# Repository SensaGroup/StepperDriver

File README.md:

# SENSA Smart Stepper Driver 

### Main features
- on-board ATMEGA328/P
- A4988 module 
- CAN Bus - MCP25625
- Encoder and switch support

## What is the SENSA Smart Stepper Driver?
The SENSA Smart Stepper Driver is an add-on module for a stepper motor and houses all features needed to gain full control of your stepper motor.
Next to the on-board CAN Bus, the driver can also be controlled through USART or I2C.

### ATMEGA328/P
The ATMEGA328/P controls the whole board which is equipped with the Arduino platform.
It runs our [open-source code](), which can be easily modified for any project.

### A4988 module
We have chosen the easily accessible A4988 stepper driver module. It has all features that are needed and it is easy to control.

### MCP25625
The CAN Bus is a very robust communication protocol, which supports up to 1Mb/s speeds and it only requires 3 wires for it to work (CANH, CANL, GND).
The [MCP25625](http://ww1.microchip.com/downloads/en/DeviceDoc/20005282B.pdf) is a CAN controller with an integrated transceiver, meaning it doesn't take up much space.

### Encoder and switches
We have added a connector for an encoder, whose pins are connected to interrupt pins of the ATMEGA328/P. 
Two switches can be also added to the board via a connector, which can help you add control to your project. 

## Images

## Sponsored by AISLER
### Develop and manufacture your own premium boards at [aisler.net](https://aisler.net/)

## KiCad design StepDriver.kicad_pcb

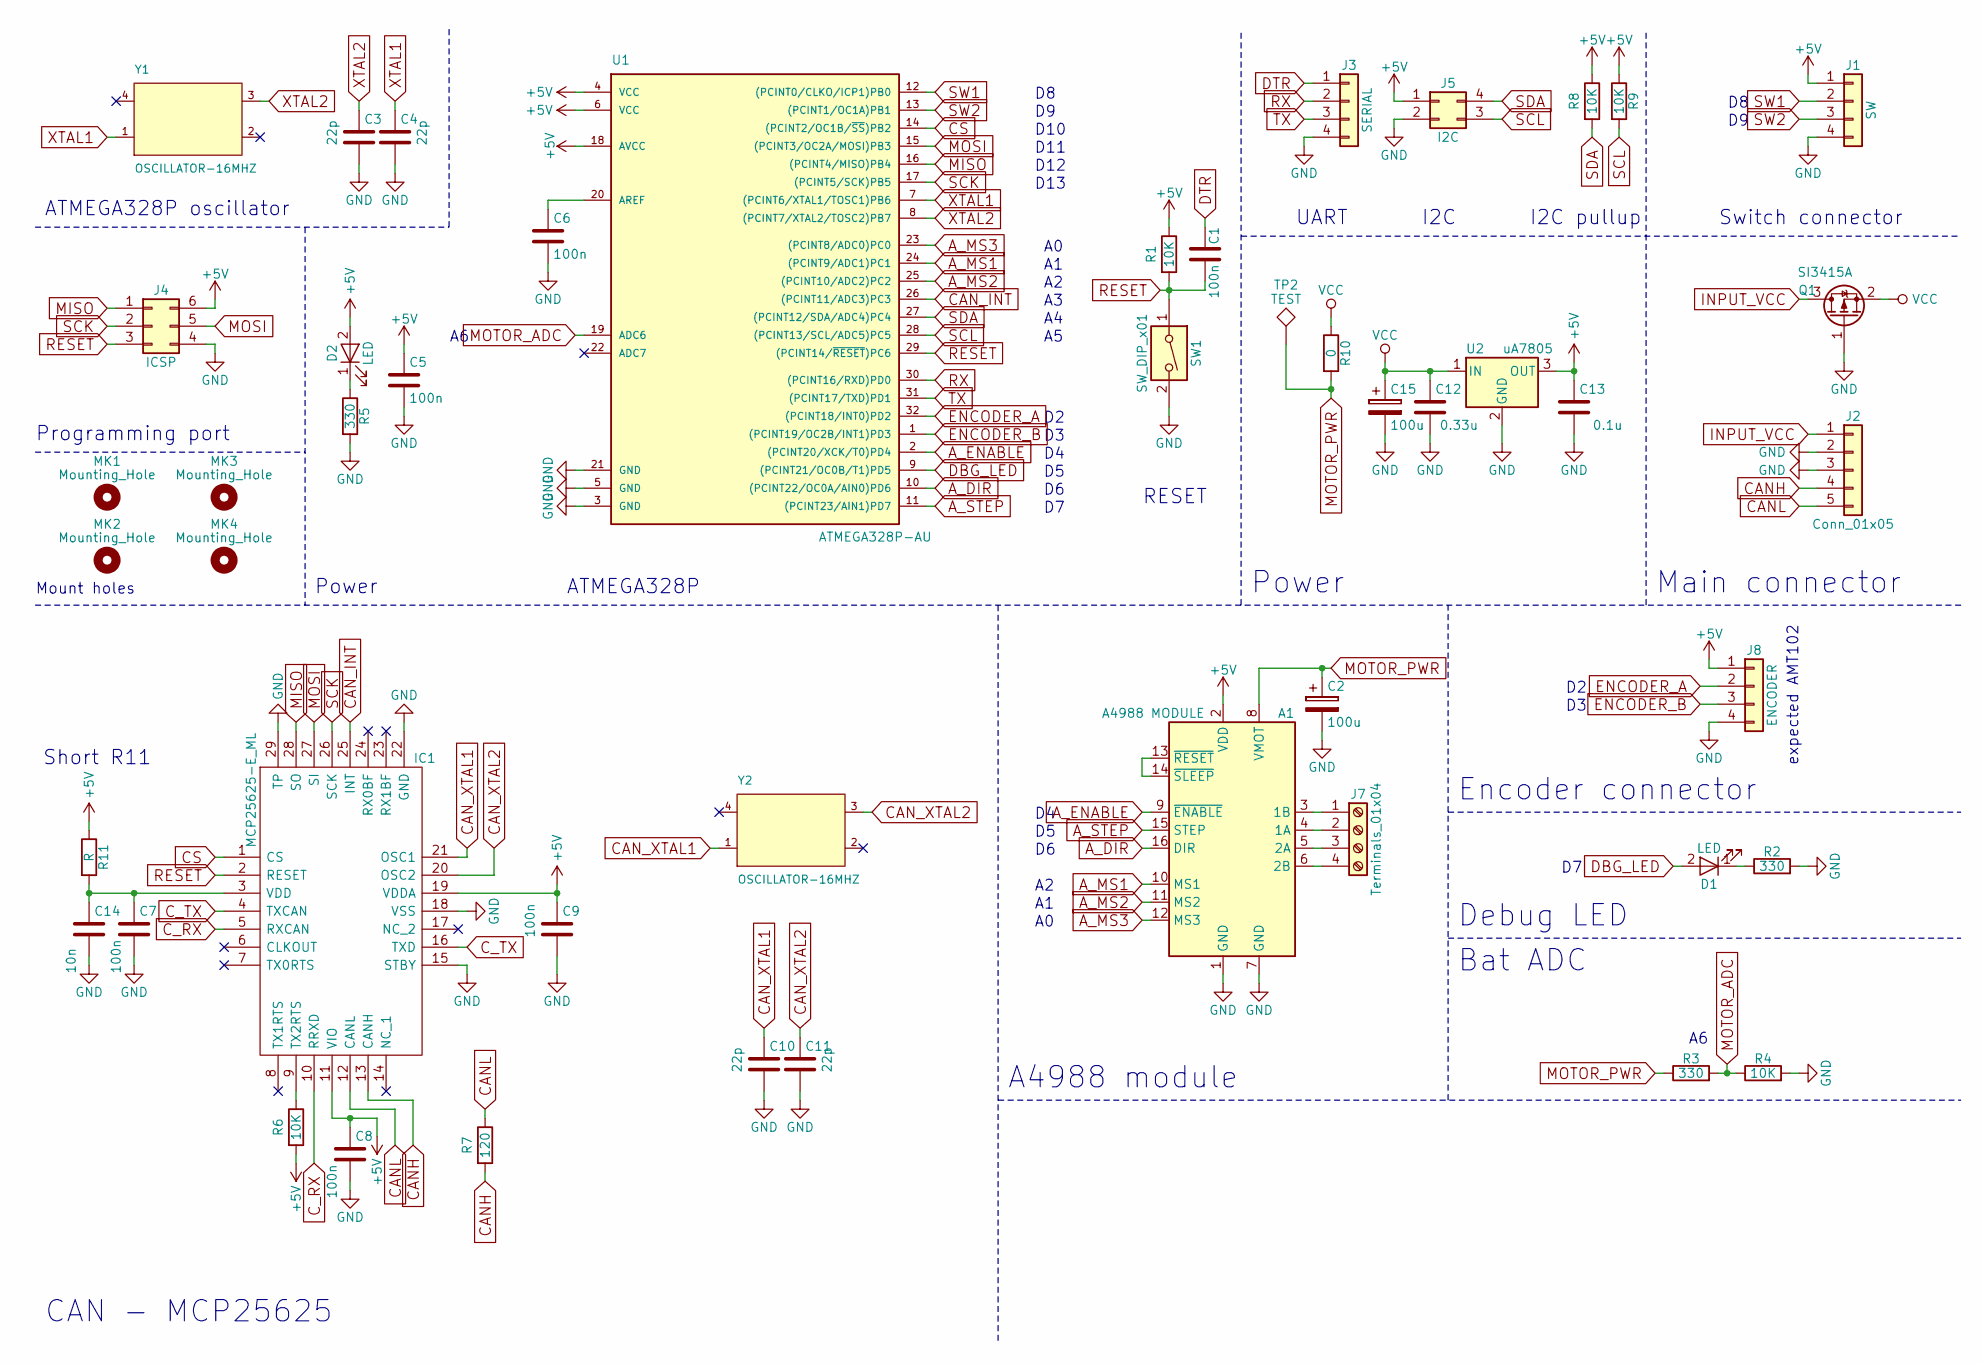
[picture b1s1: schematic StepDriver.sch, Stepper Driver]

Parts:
A1: A4988 MODULE; Pololu_Breakout-16_15.2x20.3mm
C1, C5, C6, C7, C8, C9: 100n; C_0603
C2, C15: 100u; CP_Elec_3x5.3
C3, C4, C10, C11: 22p; C_0603
C12: 0.33u; C_0603
C13: 0.1u; C_0603
C14: 10n; C_0603
D1, D2: LED; LED_0603
IC1: MCP25625-E_ML; QFN65P600X600X100-29N-D; Manufacturer_Part_Number MCP25625-E/ML
J1: SW; TerminalBlock_Phoenix_MPT-2.54mm_4pol
J2: Conn_01x05; TerminalBlock_Phoenix_MPT-2.54mm_5pol
J3: SERIAL; TerminalBlock_Phoenix_MPT-2.54mm_4pol
J4: ICSP; Pin_Header_Straight_1x06_Pitch1.27mm_SMD_Pin1Left
J5: I2C; Pin_Header_Straight_2x02_Pitch2.00mm
J7: Terminals_01x04; TerminalBlock_Phoenix_MPT-2.54mm_4pol
J8: ENCODER; TerminalBlock_Phoenix_MPT-2.54mm_4pol
MK1, MK2, MK3, MK4: Mounting_Hole; MountingHole_3.2mm_M3
Q1: SI3415A; SOT-23
R1, R4, R6, R8, R9: 10K; R_0603
R2, R3, R5: 330; R_0603
R7: 120; R_0603
R10: 0; R_1210
R11: R; R_0402_NoSilk
SW1: SW_DIP_x01; Pin_Header_Straight_1x02_Pitch2.00mm
TP2: TEST; SolderWirePad_single_0-8mmDrill
U1: ATMEGA328P-AU; TQFP-32_7x7mm_Pitch0.8mm
U2: uA7805; SOT-89-3
Y1, Y2: OSCILLATOR-16MHZ; Oscillator_SMD_Abracon_ASE-4pin_3.2x2.5mm

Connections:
+5V: A1.2 (VDD), C5.1, C8.1, C9.1, C13.1, D2.2 (A), IC1.11 (VIO), IC1.19 (VDDA), J1.1, J4.6, J5.1, J8.1, R1.1, R6.2, R8.1, R9.1, R11.1, U1.4 (VCC), U1.6 (VCC), U1.18 (AVCC), U2.3 (OUT)
A_DIR: A1.16 (DIR), U1.10 ((PCINT22/OC0A/AIN0)PD6)
A_ENABLE: A1.9 (~ENABLE), U1.2 ((PCINT20/XCK/T0)PD4)
A_MS1: A1.10 (MS1), U1.24 ((PCINT9/ADC1)PC1)
A_MS2: A1.11 (MS2), U1.25 ((PCINT10/ADC2)PC2)
A_MS3: A1.12 (MS3), U1.23 ((PCINT8/ADC0)PC0)
A_STEP: A1.15 (STEP), U1.11 ((PCINT23/AIN1)PD7)
CANH: IC1.13 (CANH), J2.4, R7.2
CANL: IC1.12 (CANL), J2.5, R7.1
CAN_INT: IC1.25 (INT), U1.26 ((PCINT11/ADC3)PC3)
CAN_XTAL1: C10.1, IC1.21 (OSC1), Y2.1 (EN)
CAN_XTAL2: C11.1, IC1.20 (OSC2), Y2.3 (OUT)
CS: IC1.1 (CS), U1.14 ((PCINT2/OC1B/~SS~)PB2)
C_RX: IC1.5 (RXCAN), IC1.10 (RRXD)
C_TX: IC1.4 (TXCAN), IC1.16 (TXD)
DBG_LED: D1.2 (A), U1.9 ((PCINT21/OC0B/T1)PD5)
DTR: C1.1, J3.1
ENCODER_A: J8.2, U1.32 ((PCINT18/INT0)PD2)
ENCODER_B: J8.3, U1.1 ((PCINT19/OC2B/INT1)PD3)
GND: A1.1 (GND), A1.7 (GND), C2.2, C3.2, C4.2, C5.2, C6.2, C7.2, C8.2, C9.2, C10.2, C11.2, C12.2, C13.2, C14.2, C15.2, IC1.15 (STBY), IC1.18 (VSS), IC1.22 (GND), IC1.29 (TP), J1.4, J2.2, J2.3, J3.4, J4.4, J5.2, J8.4, Q1.1 (G), R2.2, R4.2, R5.2, SW1.2, U1.3 (GND), U1.5 (GND), U1.21 (GND), U2.2 (GND); also elsewhere on the board
INPUT_VCC: J2.1, Q1.3 (D)
MISO: IC1.28 (SO), J4.1, U1.16 ((PCINT4/MISO)PB4)
MOSI: IC1.27 (SI), J4.5, U1.15 ((PCINT3/OC2A/MOSI)PB3)
MOTOR_ADC: R3.2, R4.1, U1.19 (ADC6)
MOTOR_PWR: A1.8 (VMOT), C2.1, R3.1, R10.2, TP2.1
unnamed: A1.3 (1B), J7.1
unnamed: A1.4 (1A), J7.2
unnamed: A1.5 (2A), J7.3
unnamed: A1.6 (2B), J7.4
unnamed: A1.13 (~RESET), A1.14 (~SLEEP)
unnamed: C6.1, U1.20 (AREF)
unnamed: C7.1, C14.1, IC1.3 (VDD), R11.2
unnamed: D1.1 (K), R2.1
unnamed: D2.1 (K), R5.1
unnamed: IC1.9 (TX2RTS), R6.1
RESET: C1.2, IC1.2 (RESET), J4.3, R1.2, SW1.1, U1.29 ((PCINT14/~RESET~)PC6); also elsewhere on the board
RX: J3.2, U1.30 ((PCINT16/RXD)PD0)
SCK: IC1.26 (SCK), J4.2, U1.17 ((PCINT5/SCK)PB5)
SCL: J5.3, R9.2, U1.28 ((PCINT13/SCL/ADC5)PC5)
SDA: J5.4, R8.2, U1.27 ((PCINT12/SDA/ADC4)PC4)
SW1: J1.2, U1.12 ((PCINT0/CLKO/ICP1)PB0)
SW2: J1.3, U1.13 ((PCINT1/OC1A)PB1)
TX: J3.3, U1.31 ((PCINT17/TXD)PD1)
VCC: C12.1, C15.1, Q1.2 (S), R10.1, U2.1 (IN)
XTAL1: C4.1, U1.7 ((PCINT6/XTAL1/TOSC1)PB6), Y1.1 (EN)
XTAL2: C3.1, U1.8 ((PCINT7/XTAL2/TOSC2)PB7), Y1.3 (OUT)

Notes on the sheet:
expected AMT102
D10
D11
D12
D13
Mount holes
ATMEGA328P oscillator
ATMEGA328P
Power
UART
I2C
I2C pullup
Switch connector
Main connector
Power
A4988 module
Bat ADC
Debug LED
Encoder connector
CAN - MCP25625
Programming port
RESET
Short R11

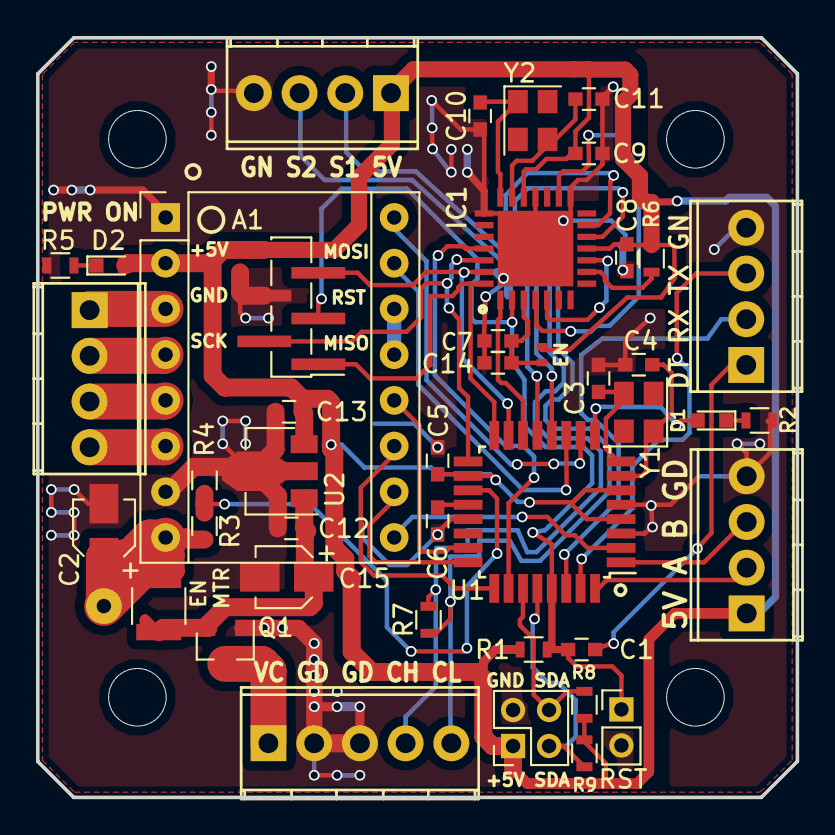
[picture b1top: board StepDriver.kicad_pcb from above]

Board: 2 copper layers, 42.2 x 42.2 mm, 48 parts (0 on the bottom side), 46 nets.

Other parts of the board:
RST: SW_DIP_x01; Pin_Header_Straight_1x02_Pitch2.00mm

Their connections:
GND: RST.2; also elsewhere on the board
RESET: RST.1; also elsewhere on the board

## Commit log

2018-10-14 All files
2018-10-25 Small changes, added step and refined schematic and images
2018-10-25 .jpg...
2018-10-25 Readme
2018-10-25 change board
2018-10-25 testing align
2018-10-25 New images
2018-10-25 readme modif
